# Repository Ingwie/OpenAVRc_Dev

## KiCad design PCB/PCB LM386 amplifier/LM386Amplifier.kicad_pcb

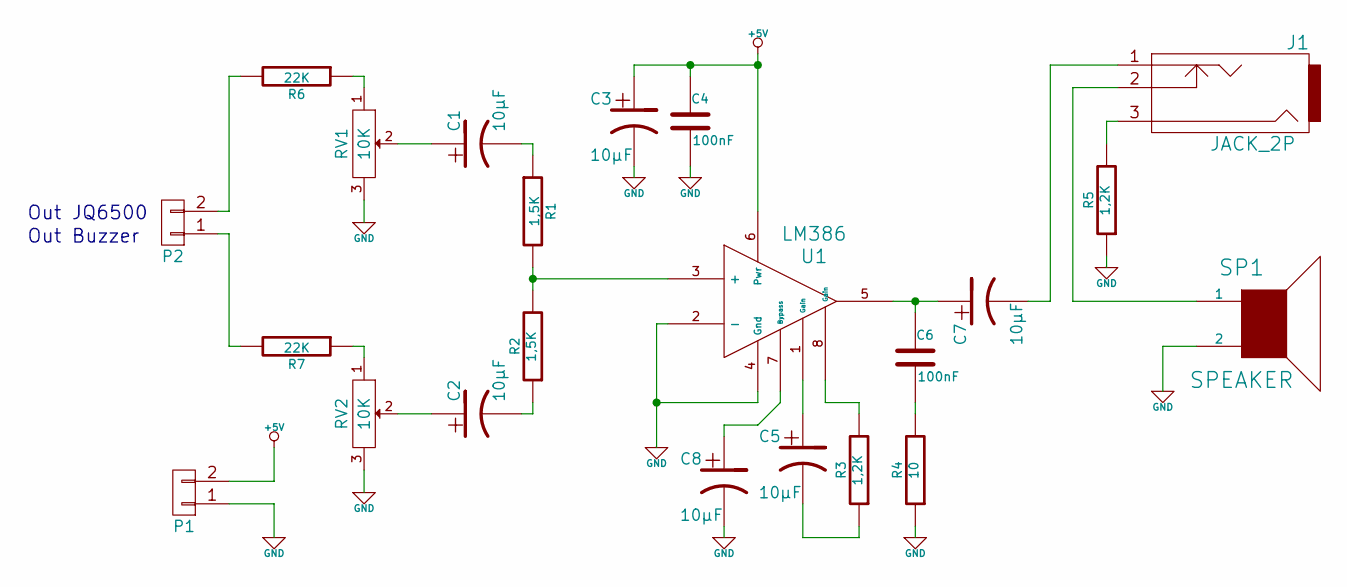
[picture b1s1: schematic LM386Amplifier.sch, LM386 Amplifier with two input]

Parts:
C1, C2, C3: 10µF; CP_Radial_D6.3mm_P2.50mm
C4, C6: 100nF; C_Rect_L7.0mm_W2.0mm_P5.00mm
C5, C7, C8: 10µF; CP_Radial_Tantal_D6.0mm_P2.50mm
J1: JACK_2P; Pin_Header_Straight_1x03_Pitch2.54mm
P1, P2: CONN_01X02; Pin_Header_Straight_1x02_Pitch2.54mm
R1, R2: 1,5K; R_Axial_DIN0204_L3.6mm_D1.6mm_P2.54mm_Vertical
R3, R5: 1,2K; R_Axial_DIN0204_L3.6mm_D1.6mm_P2.54mm_Vertical
R4: 10; R_Axial_DIN0204_L3.6mm_D1.6mm_P2.54mm_Vertical
R6, R7: 22K; R_Axial_DIN0204_L3.6mm_D1.6mm_P2.54mm_Vertical
RV1, RV2: 10K; Potentiometer_Trimmer_Bourns_3296W.kicad_mod
SP1: SPEAKER; Pin_Header_Straight_1x02_Pitch2.54mm
U1: LM386; DIP-8_W7.62mm_LongPads

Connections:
+5V: C3.1, C4.1, P1.2, U1.6 (Pwr)
GND: C3.2, C4.2, C8.2, P1.1, R4.1, R5.1, RV1.3, RV2.3, SP1.2, U1.2 (-), U1.4 (Gnd)
unnamed: C1.1, RV1.2
unnamed: C1.2, R1.1
unnamed: C2.1, RV2.2
unnamed: C2.2, R2.1
unnamed: C5.1, U1.1 (Gain)
unnamed: C5.2, R3.1
unnamed: C6.1, C7.1, U1.5
unnamed: C6.2, R4.2
unnamed: C7.2, J1.1
unnamed: C8.1, U1.7 (Bypass)
unnamed: J1.2, SP1.1
unnamed: J1.3, R5.2
unnamed: P2.1, R7.2
unnamed: P2.2, R6.2
unnamed: R1.2, R2.2, U1.3 (+)
unnamed: R3.2, U1.8 (Gain)
unnamed: R6.1, RV1.1
unnamed: R7.1, RV2.1

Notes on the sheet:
Out Buzzer
Out JQ6500

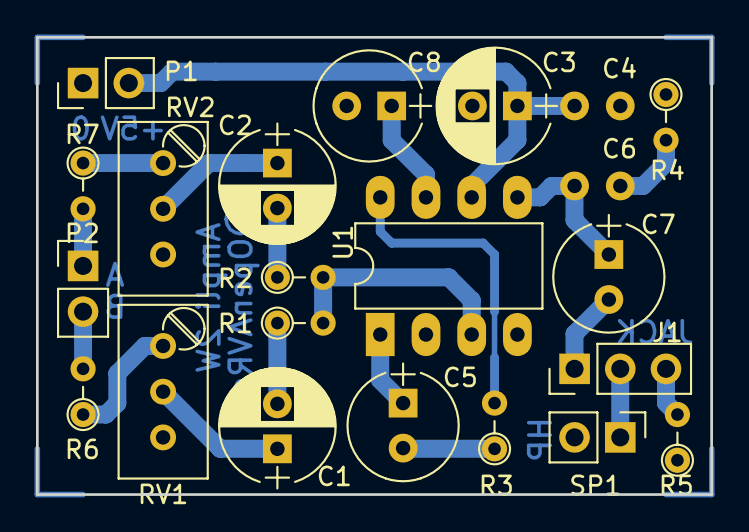
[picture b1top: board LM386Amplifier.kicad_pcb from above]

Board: 2 copper layers, 37.5 x 25.4 mm, 22 parts (0 on the bottom side), 20 nets.

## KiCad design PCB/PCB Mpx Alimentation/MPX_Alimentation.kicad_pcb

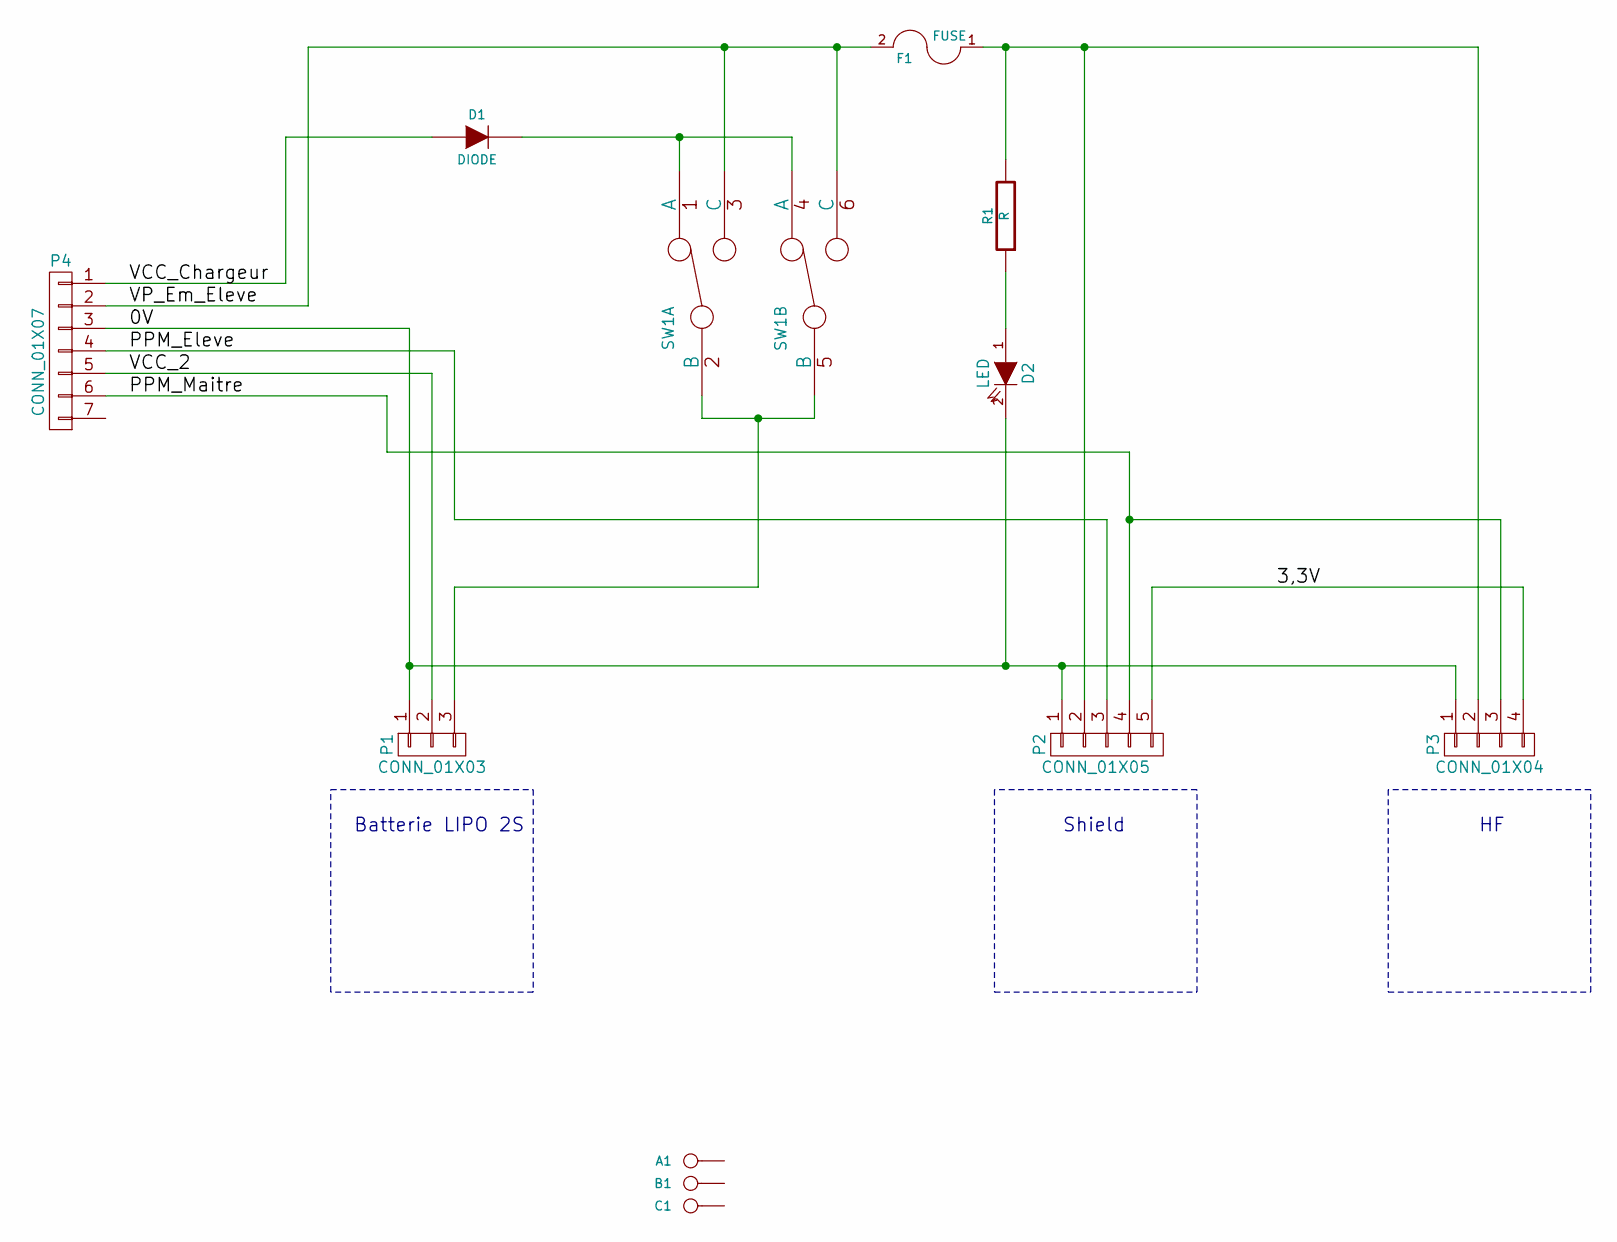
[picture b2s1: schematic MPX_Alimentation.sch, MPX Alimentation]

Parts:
A1: CONN_1; MountingHole_2.2mm_M2
B1: CONN_1; MountingHole_2.2mm_M2
C1: CONN_1; MountingHole_2.2mm_M2
D1: DIODE; D_DO-201_P15.24mm_Horizontal
D2: LED; LED_D3.0mm
F1: FUSE; Fuseholder5x20_horiz_open_universal_Type-III
P1: CONN_01X03; Pin_Header_Angled_1x03_Pitch2.54mm
P2: CONN_01X05; Pin_Header_Angled_1x05_Pitch2.54mm
P3: CONN_01X04; Pin_Header_Angled_1x04_Pitch2.54mm
P4: CONN_01X07; Embase_Din8_Mpx
R1: R; R_Axial_DIN0207_L6.3mm_D2.5mm_P10.16mm_Horizontal
SW1: DUAL_SWITCH_INV; SW_CuK_JS202011CQN_DPDT_Straight

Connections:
/0V: D2.2 (K), P1.1, P2.1, P3.1, P4.3
/3,3V: P2.5, P3.4
/PPM_Eleve: P2.3, P4.4
/PPM_Maitre: P2.4, P3.3, P4.6
/VCC_2: P1.2, P4.5
/VCC_Chargeur: D1.1 (A), P4.1
/VP_Em_Eleve: F1.2, P4.2, SW1.3 (C), SW1.6 (C)
unnamed: D1.2 (K), SW1.1 (A), SW1.4 (A)
unnamed: D2.1 (A), R1.1
unnamed: F1.1, P2.2, P3.2, R1.2
unnamed: P1.3, SW1.2 (B), SW1.5 (B)

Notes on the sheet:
Batterie LIPO 2S
Shield

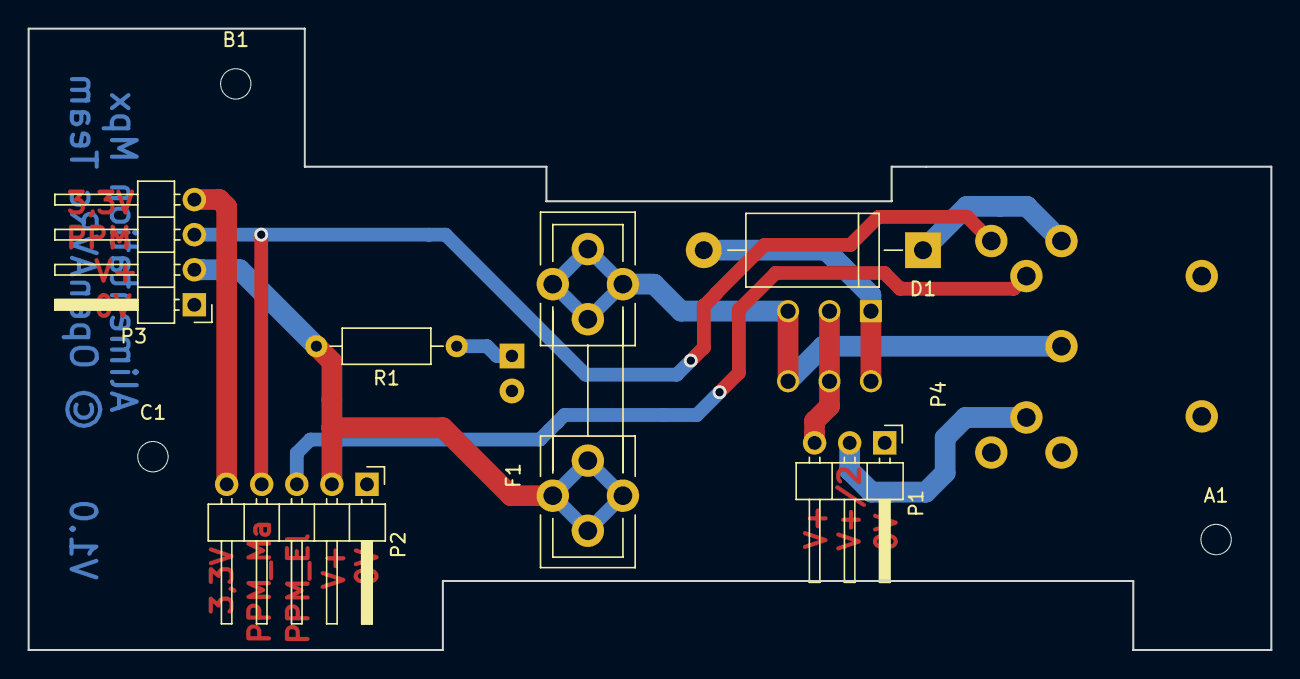
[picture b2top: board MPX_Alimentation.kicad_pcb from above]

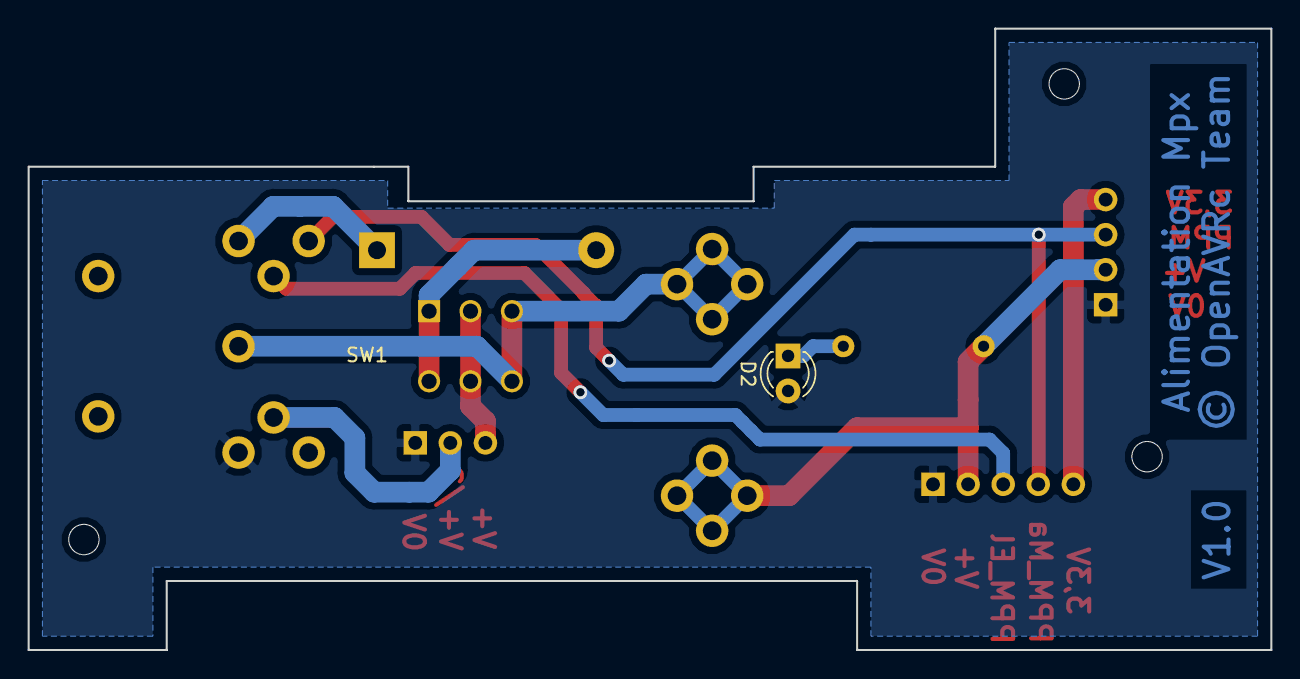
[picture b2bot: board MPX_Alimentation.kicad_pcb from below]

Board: 2 copper layers, 90.0 x 45.0 mm, 12 parts (2 on the bottom side), 11 nets.

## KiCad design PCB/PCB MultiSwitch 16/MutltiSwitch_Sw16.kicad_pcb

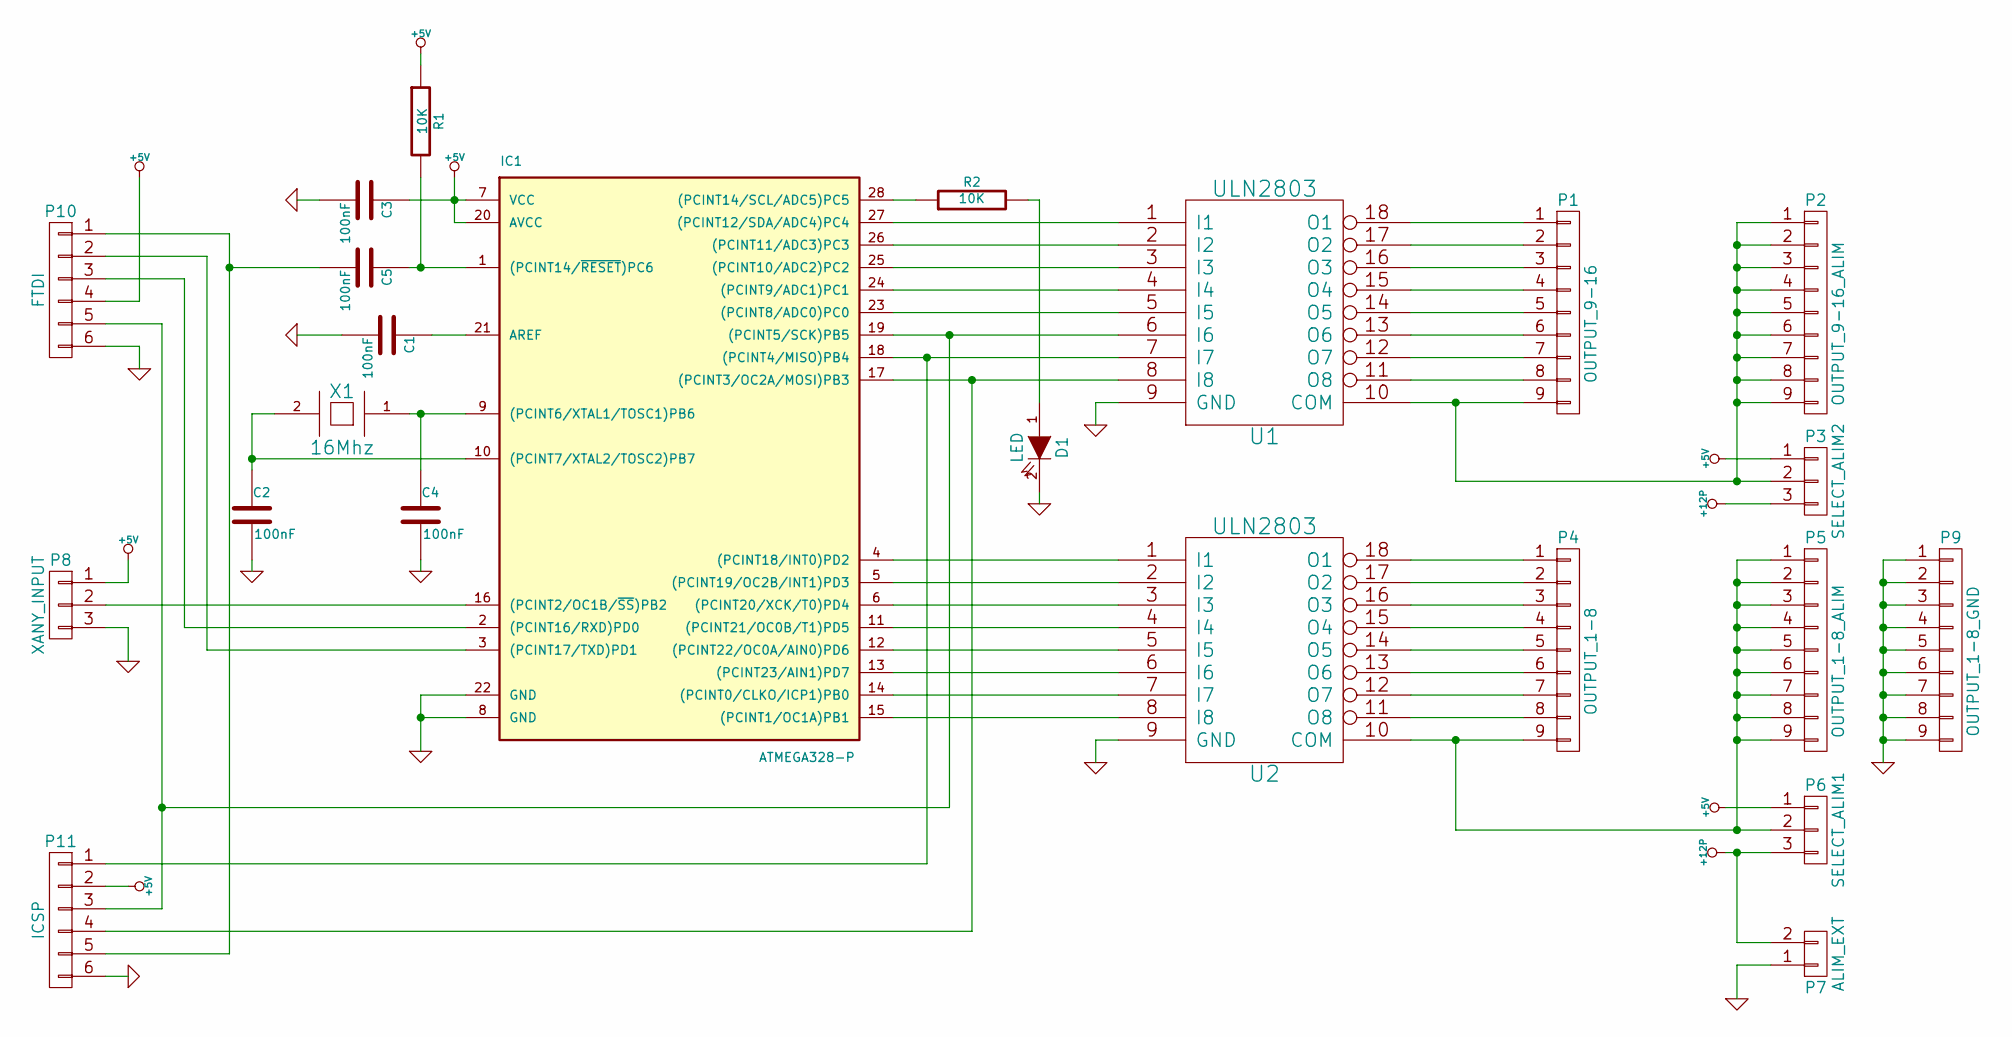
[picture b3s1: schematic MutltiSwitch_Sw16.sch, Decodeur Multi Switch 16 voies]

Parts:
C1, C2, C3, C4, C5: 100nF; C_1206
D1: LED; LED_1206
IC1: ATMEGA328-P; DIP-28_W7.62mm_LongPads
P1: OUTPUT_9-16; Pin_Header_Straight_1x09_Pitch2.54mm
P2: OUTPUT_9-16_ALIM; Pin_Header_Straight_1x09_Pitch2.54mm
P3: SELECT_ALIM2; Pin_Header_Straight_1x03_Pitch2.54mm
P4: OUTPUT_1-8; Pin_Header_Straight_1x09_Pitch2.54mm
P5: OUTPUT_1-8_ALIM; Pin_Header_Straight_1x09_Pitch2.54mm
P6: SELECT_ALIM1; Pin_Header_Straight_1x03_Pitch2.54mm
P7: ALIM_EXT; XT60_F
P8: XANY_INPUT; Pin_Header_Straight_1x03_Pitch2.54mm
P9: OUTPUT_1-8_GND; Pin_Header_Straight_1x09_Pitch2.54mm
P10: FTDI; Pin_Header_Straight_2x03_Pitch2.54mm
P11: ICSP; Pin_Header_Straight_2x03_Pitch2.54mm
R1, R2: 10K; R_1206
U1, U2: ULN2803; DIP-18_W7.62mm_LongPads
X1: 16Mhz; HC-39

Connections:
+5V: C3.1, IC1.7 (VCC), IC1.20 (AVCC), P3.1, P6.1, P8.1, P10.4, P11.2, R1.1
+12P: P3.3, P6.3, P7.2
GND: C1.2, C2.2, C3.2, C4.2, D1.2 (K), IC1.8 (GND), IC1.22 (GND), P7.1, P8.3, P9.1, P9.2, P9.3, P9.4, P9.5, P9.6, P9.7, P9.8, P9.9, P10.6, P11.6, U1.9 (GND), U2.9 (GND)
unnamed: C1.1, IC1.21 (AREF)
unnamed: C2.1, IC1.10 ((PCINT7/XTAL2/TOSC2)PB7), X1.2
unnamed: C4.1, IC1.9 ((PCINT6/XTAL1/TOSC1)PB6), X1.1
unnamed: C5.1, IC1.1 ((PCINT14/~RESET~)PC6), R1.2
unnamed: C5.2, P10.1, P11.5
unnamed: D1.1 (A), R2.2
unnamed: IC1.2 ((PCINT16/RXD)PD0), P10.3
unnamed: IC1.3 ((PCINT17/TXD)PD1), P10.2
unnamed: IC1.4 ((PCINT18/INT0)PD2), U2.1 (I1)
unnamed: IC1.5 ((PCINT19/OC2B/INT1)PD3), U2.2 (I2)
unnamed: IC1.6 ((PCINT20/XCK/T0)PD4), U2.3 (I3)
unnamed: IC1.11 ((PCINT21/OC0B/T1)PD5), U2.4 (I4)
unnamed: IC1.12 ((PCINT22/OC0A/AIN0)PD6), U2.5 (I5)
unnamed: IC1.13 ((PCINT23/AIN1)PD7), U2.6 (I6)
unnamed: IC1.14 ((PCINT0/CLKO/ICP1)PB0), U2.7 (I7)
unnamed: IC1.15 ((PCINT1/OC1A)PB1), U2.8 (I8)
unnamed: IC1.16 ((PCINT2/OC1B/~SS~)PB2), P8.2
unnamed: IC1.17 ((PCINT3/OC2A/MOSI)PB3), P11.4, U1.8 (I8)
unnamed: IC1.18 ((PCINT4/MISO)PB4), P11.1, U1.7 (I7)
unnamed: IC1.19 ((PCINT5/SCK)PB5), P10.5, P11.3, U1.6 (I6)
unnamed: IC1.23 ((PCINT8/ADC0)PC0), U1.5 (I5)
unnamed: IC1.24 ((PCINT9/ADC1)PC1), U1.4 (I4)
unnamed: IC1.25 ((PCINT10/ADC2)PC2), U1.3 (I3)
unnamed: IC1.26 ((PCINT11/ADC3)PC3), U1.2 (I2)
unnamed: IC1.27 ((PCINT12/SDA/ADC4)PC4), U1.1 (I1)
unnamed: IC1.28 ((PCINT14/SCL/ADC5)PC5), R2.1
unnamed: P1.1, U1.18 (O1)
unnamed: P1.2, U1.17 (O2)
unnamed: P1.3, U1.16 (O3)
unnamed: P1.4, U1.15 (O4)
unnamed: P1.5, U1.14 (O5)
unnamed: P1.6, U1.13 (O6)
unnamed: P1.7, U1.12 (O7)
unnamed: P1.8, U1.11 (O8)
unnamed: P1.9, P2.1, P2.2, P2.3, P2.4, P2.5, P2.6, P2.7, P2.8, P2.9, P3.2, U1.10 (COM)
unnamed: P4.1, U2.18 (O1)
unnamed: P4.2, U2.17 (O2)
unnamed: P4.3, U2.16 (O3)
unnamed: P4.4, U2.15 (O4)
unnamed: P4.5, U2.14 (O5)
unnamed: P4.6, U2.13 (O6)
unnamed: P4.7, U2.12 (O7)
unnamed: P4.8, U2.11 (O8)
unnamed: P4.9, P5.1, P5.2, P5.3, P5.4, P5.5, P5.6, P5.7, P5.8, P5.9, P6.2, U2.10 (COM)

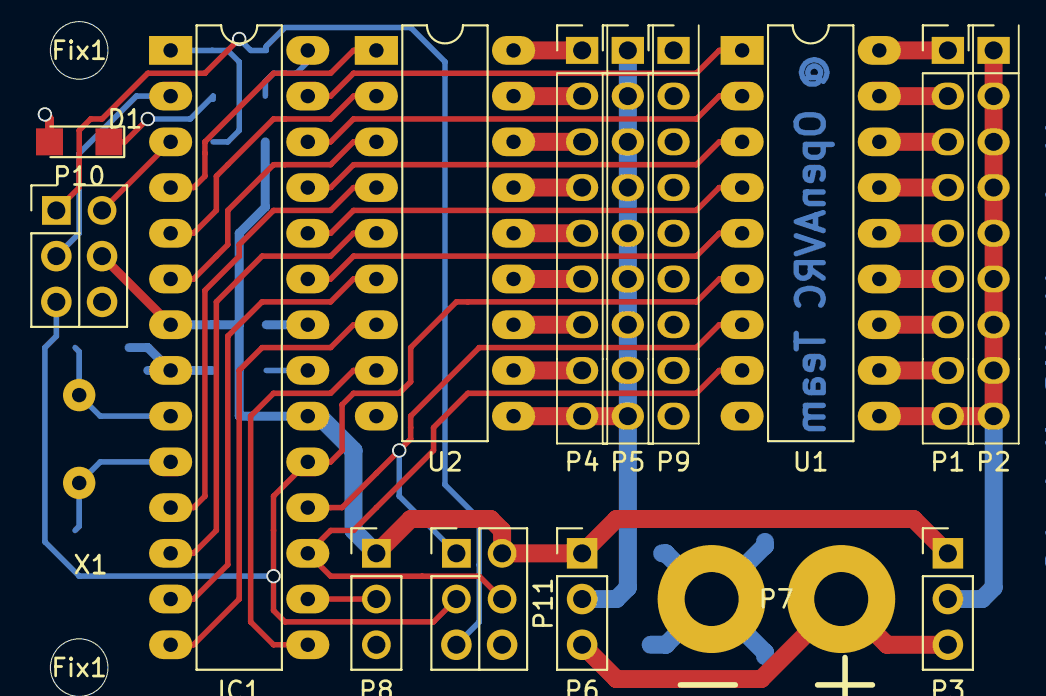
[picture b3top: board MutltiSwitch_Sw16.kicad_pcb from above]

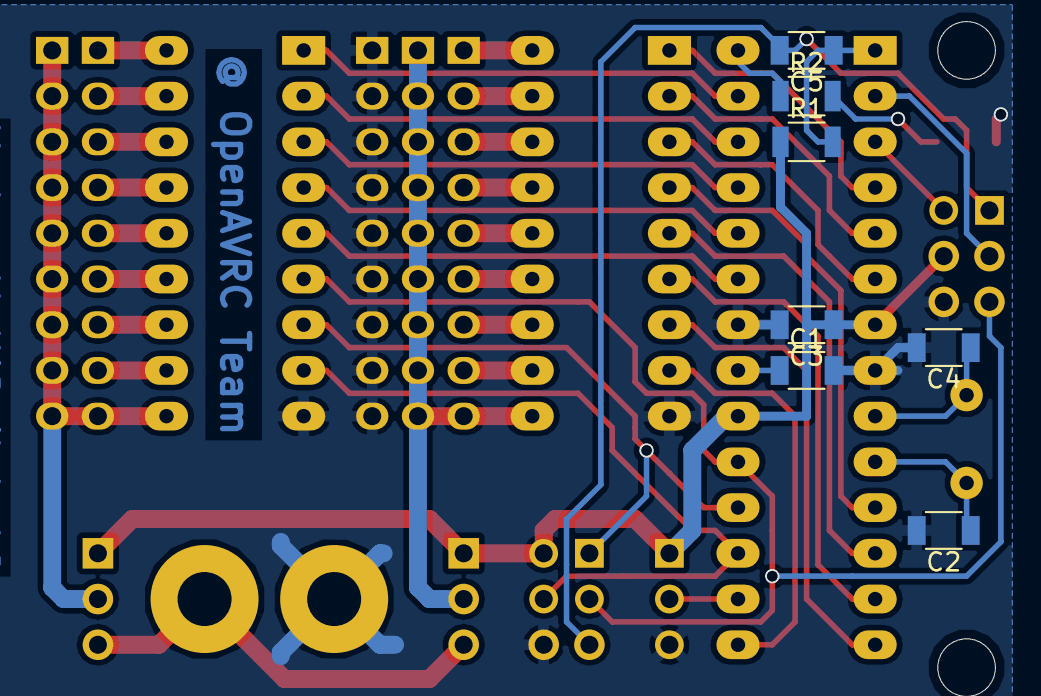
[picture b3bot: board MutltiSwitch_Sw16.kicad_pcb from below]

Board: 2 copper layers, 27 parts (7 on the bottom side), 47 nets.

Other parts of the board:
Fix1, Fix1#2, Fix1#3, Fix1#4: MountingHole_3.2mm_M3

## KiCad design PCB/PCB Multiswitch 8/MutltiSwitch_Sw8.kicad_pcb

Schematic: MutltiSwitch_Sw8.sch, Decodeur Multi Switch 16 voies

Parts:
C1, C2, C3: 100nF; C_1206
D1: LED; LED_1206
IC1: ATTINY84-P; DIP-14_W7.62mm_LongPads
IC2: ULN2803; DIP-18_W7.62mm_LongPads
P1: OUTPUT_1-8; Pin_Header_Straight_1x09_Pitch2.54mm
P8: XANY_INPUT; Pin_Header_Straight_1x03_Pitch2.54mm
R2: 470; R_1206
X1: 16Mhz; HC-39

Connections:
+5V: C1.1, IC1.1 (VCC), P8.2
GND: C1.2, C2.2, C3.2, D1.2 (K), IC1.14 (GND), IC2.9 (GND), P8.3
unnamed: C2.1, IC1.3 ((PCINT9/XTAL2)PB1), X1.2
unnamed: C3.1, IC1.2 ((PCINT8/CLKI/XTAL1)PB0), X1.1
unnamed: D1.1 (A), R2.2
unnamed: IC1.4 ((PCINT11/dW/~RESET~)PB3), R2.1
unnamed: IC1.5 ((PCINT10/CKOUT/OC0A/INT0)PB2), P8.1
unnamed: IC1.6 ((PCINT7/ICP/OC0B/ADC7)PA7), IC2.8 (I8)
unnamed: IC1.7 ((PCINT6/SDA/DI/MOSI/OC1A/ADC6)PA6), IC2.7 (I7)
unnamed: IC1.8 ((PCINT5/DO/MISO/OC1B/ADC5)PA5), IC2.6 (I6)
unnamed: IC1.9 ((PCINT4/USCK/SCL/T1/ADC4)PA4), IC2.5 (I5)
unnamed: IC1.10 ((PCINT3/T0/ADC3)PA3), IC2.4 (I4)
unnamed: IC1.11 ((PCINT2/AIN1/ADC2)PA2), IC2.3 (I3)
unnamed: IC1.12 ((PCINT1/AIN0/ADC1)PA1), IC2.2 (I2)
unnamed: IC1.13 ((PCINT0/AREF/ADC0)PA0), IC2.1 (I1)
unnamed: IC2.10 (COM), P1.9
unnamed: IC2.11 (O8), P1.8
unnamed: IC2.12 (O7), P1.7
unnamed: IC2.13 (O6), P1.6
unnamed: IC2.14 (O5), P1.5
unnamed: IC2.15 (O4), P1.4
unnamed: IC2.16 (O3), P1.3
unnamed: IC2.17 (O2), P1.2
unnamed: IC2.18 (O1), P1.1

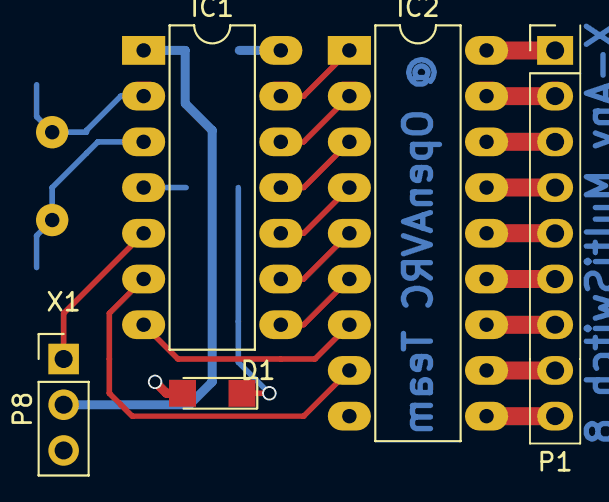
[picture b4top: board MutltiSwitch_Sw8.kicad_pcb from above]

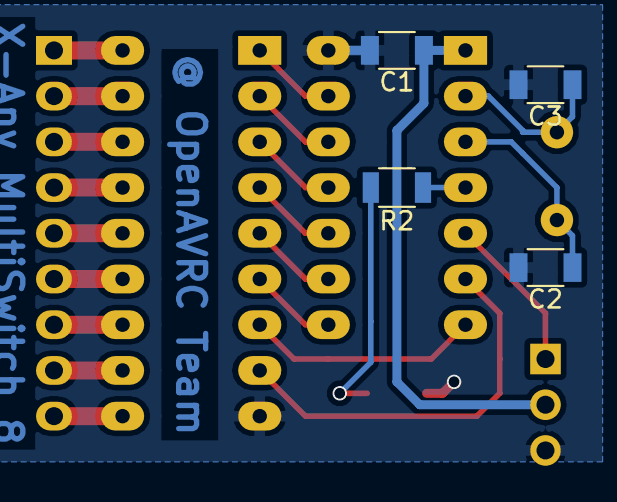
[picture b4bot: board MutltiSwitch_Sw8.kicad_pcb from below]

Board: 2 copper layers, 10 parts (4 on the bottom side), 24 nets.

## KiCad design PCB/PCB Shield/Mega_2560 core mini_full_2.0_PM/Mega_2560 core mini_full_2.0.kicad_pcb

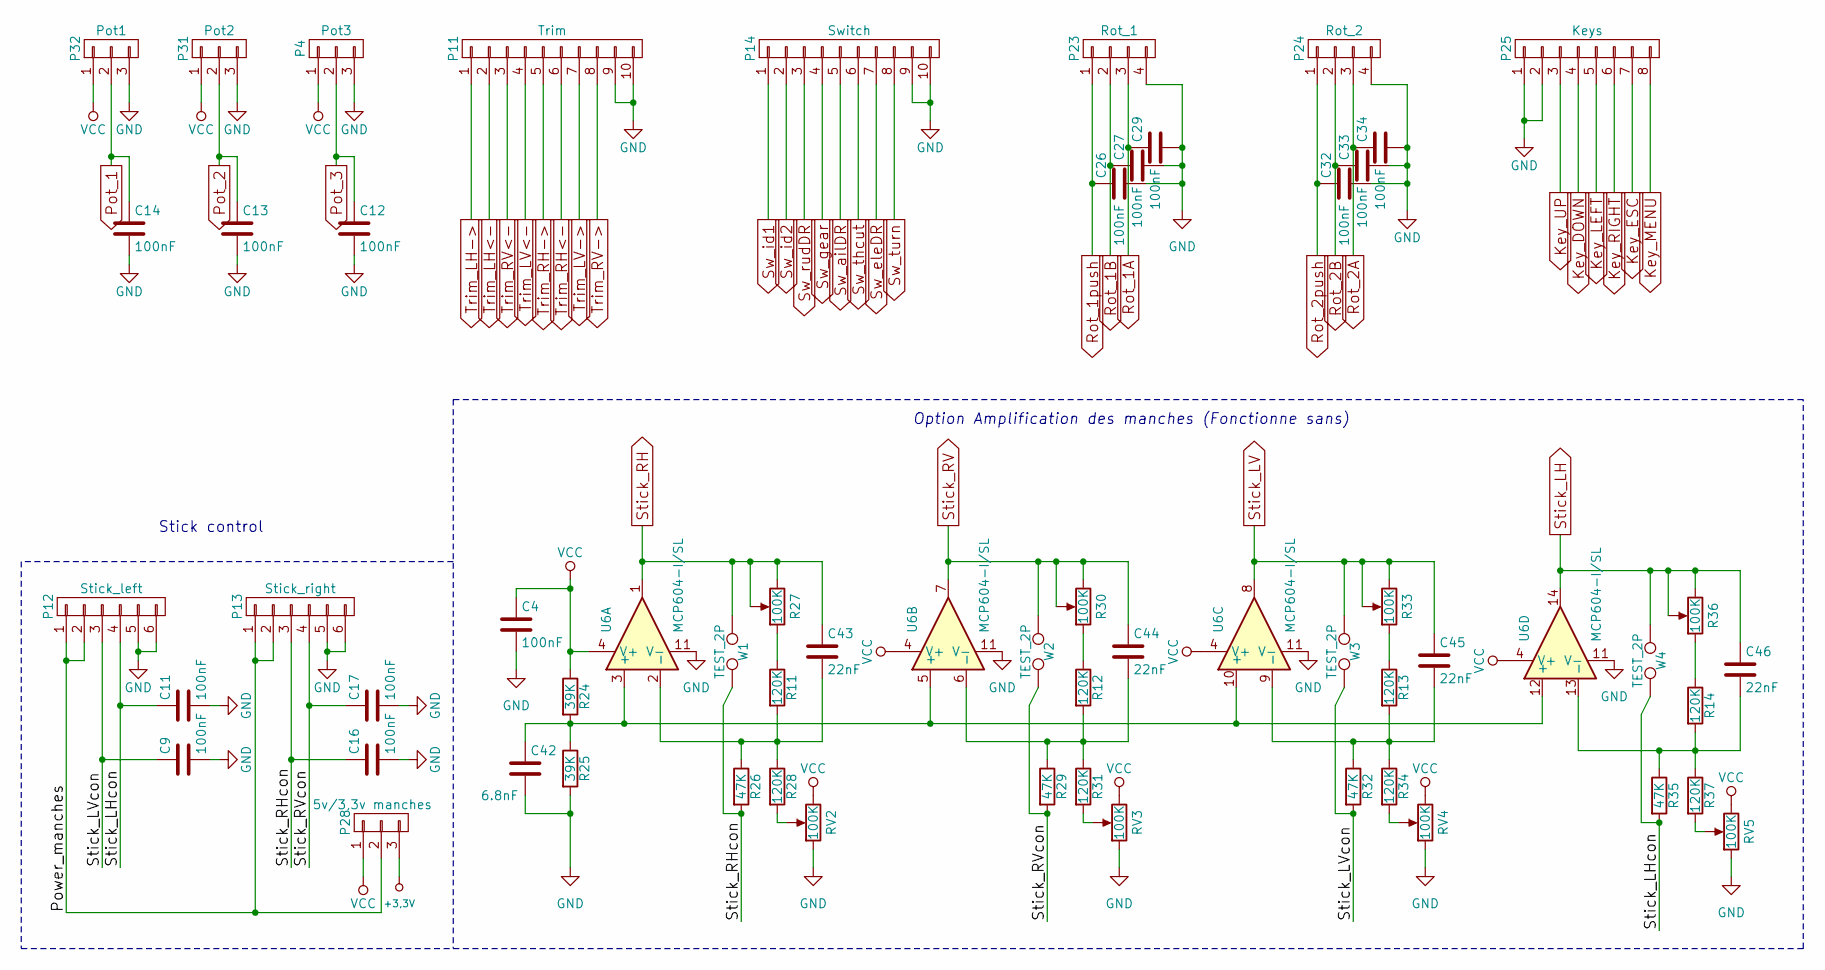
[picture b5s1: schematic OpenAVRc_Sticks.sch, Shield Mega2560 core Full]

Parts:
C4, C9, C11, C12, C13, C14, C16, C17, C26, C27, C29, C32, C33, C34: 100nF; C_1206
C42: 6.8nF; C_1206
C43, C44, C45, C46: 22nF; C_1206
P4: Pot3; Pin_Header_Straight_1x03_Pitch2.54mm
P11: Trim; Pin_Header_Straight_2x05_Pitch2.54mm
P12: Stick_left; Pin_Header_Straight_2x03_Pitch2.54mm
P13: Stick_right; Pin_Header_Straight_1x06_Pitch2.54mm
P14: Switch; Pin_Header_Straight_2x05_Pitch2.54mm
P23: Rot_1; Pin_Header_Straight_1x04_Pitch2.54mm
P24: Rot_2; Pin_Header_Straight_1x04_Pitch2.54mm
P25: Keys; Pin_Header_Straight_2x04_Pitch2.54mm
P28: 5v/3,3v manches; Pin_Header_Straight_1x03_Pitch2.54mm
P31: Pot2; Pin_Header_Straight_1x03_Pitch2.54mm
P32: Pot1; Pin_Header_Straight_1x03_Pitch2.54mm
R11, R12, R13, R14, R28, R31, R34, R37: 120K; R_1206
R24, R25: 39K; R_1206
R26, R29, R32, R35: 47K; R_1206
R27, R30, R33, R36: 100K; Potentiometer_Trimmer_Bourns_3296W
RV2, RV3, RV4, RV5: 100K; Potentiometer_Bourns_3296W_3-8Zoll_Inline_ScrewUp
U6: MCP604-I/SL; SOP14
W1, W2, W3, W4: TEST_2P; TESTPT

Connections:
+3.3V: P28.3; also elsewhere on the board
/OpenAVRc_Sticks/Power_manches: P12.1, P12.2, P13.1, P13.2, P28.2
/OpenAVRc_Sticks/Stick_LHcon: C11.1, P12.4, R35.2, W4.2
/OpenAVRc_Sticks/Stick_LVcon: C9.1, P12.3, R32.2, W3.2
/OpenAVRc_Sticks/Stick_RHcon: C16.1, P13.3, R26.2, W1.2
/OpenAVRc_Sticks/Stick_RVcon: C17.1, P13.4, R29.2, W2.2
GND: C4.2, C9.2, C11.2, C12.2, C13.2, C14.2, C16.2, C17.2, C26.2, C27.2, C29.2, C32.2, C33.2, C34.2, C42.2, P4.3, P11.9, P11.10, P12.5, P12.6, P13.5, P13.6, P14.9, P14.10, P23.4, P24.4, P25.1, P25.2, P31.3, P32.3, R25.2, RV2.1, RV3.1, RV4.1, RV5.1, U6.11 (V-); also elsewhere on the board
Key_DOWN: P25.4; also elsewhere on the board
Key_ESC: P25.7; also elsewhere on the board
Key_LEFT: P25.5; also elsewhere on the board
Key_MENU: P25.8; also elsewhere on the board
Key_RIGHT: P25.6; also elsewhere on the board
Key_UP: P25.3; also elsewhere on the board
unnamed: C42.1, R24.2, R25.1, U6.3 (+), U6.5 (+), U6.10 (+), U6.12 (+)
unnamed: C43.2, R11.2, R26.1, R28.1, U6.2 (-)
unnamed: C44.2, R12.2, R29.1, R31.1, U6.6 (-)
unnamed: C45.2, R13.2, R32.1, R34.1, U6.9 (-)
unnamed: C46.2, R14.2, R35.1, R37.1, U6.13 (-)
unnamed: R11.1, R27.1
unnamed: R12.1, R30.1
unnamed: R13.1, R33.1
unnamed: R14.1, R36.1
unnamed: R28.2, RV2.2
unnamed: R31.2, RV3.2
unnamed: R34.2, RV4.2
unnamed: R37.2, RV5.2
Pot_1: C14.1, P32.2; also elsewhere on the board
Pot_2: C13.1, P31.2; also elsewhere on the board
Pot_3: C12.1, P4.2; also elsewhere on the board
Rot_1A: C29.1, P23.3; also elsewhere on the board
Rot_1B: C27.1, P23.2; also elsewhere on the board
Rot_1push: C26.1, P23.1; also elsewhere on the board
Rot_2A: C34.1, P24.3; also elsewhere on the board
Rot_2B: C33.1, P24.2; also elsewhere on the board
Rot_2push: C32.1, P24.1; also elsewhere on the board
Stick_LH: C46.1, R36.2, R36.3, U6.14, W4.1; also elsewhere on the board
Stick_LV: C45.1, R33.2, R33.3, U6.8, W3.1; also elsewhere on the board
Stick_RH: C43.1, R27.2, R27.3, U6.1, W1.1; also elsewhere on the board
Stick_RV: C44.1, R30.2, R30.3, U6.7, W2.1; also elsewhere on the board
Sw_ailDR: P14.5; also elsewhere on the board
Sw_eleDR: P14.7; also elsewhere on the board
Sw_gear: P14.4; also elsewhere on the board
Sw_id1: P14.1; also elsewhere on the board
Sw_id2: P14.2; also elsewhere on the board
Sw_rudDR: P14.3; also elsewhere on the board
Sw_thcut: P14.6; also elsewhere on the board
Sw_turn: P14.8; also elsewhere on the board
Trim_LH->: P11.1; also elsewhere on the board
Trim_LH<-: P11.2; also elsewhere on the board
Trim_LV->: P11.7; also elsewhere on the board
Trim_LV<-: P11.4; also elsewhere on the board
Trim_RH->: P11.5; also elsewhere on the board
Trim_RH<-: P11.6; also elsewhere on the board
Trim_RV->: P11.8; also elsewhere on the board
Trim_RV<-: P11.3; also elsewhere on the board
VCC: C4.1, P4.1, P28.1, P31.1, P32.1, R24.1, RV2.3, RV3.3, RV4.3, RV5.3, U6.4 (V+); also elsewhere on the board

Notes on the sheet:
Stick control
Option Amplification des manches (Fonctionne sans)

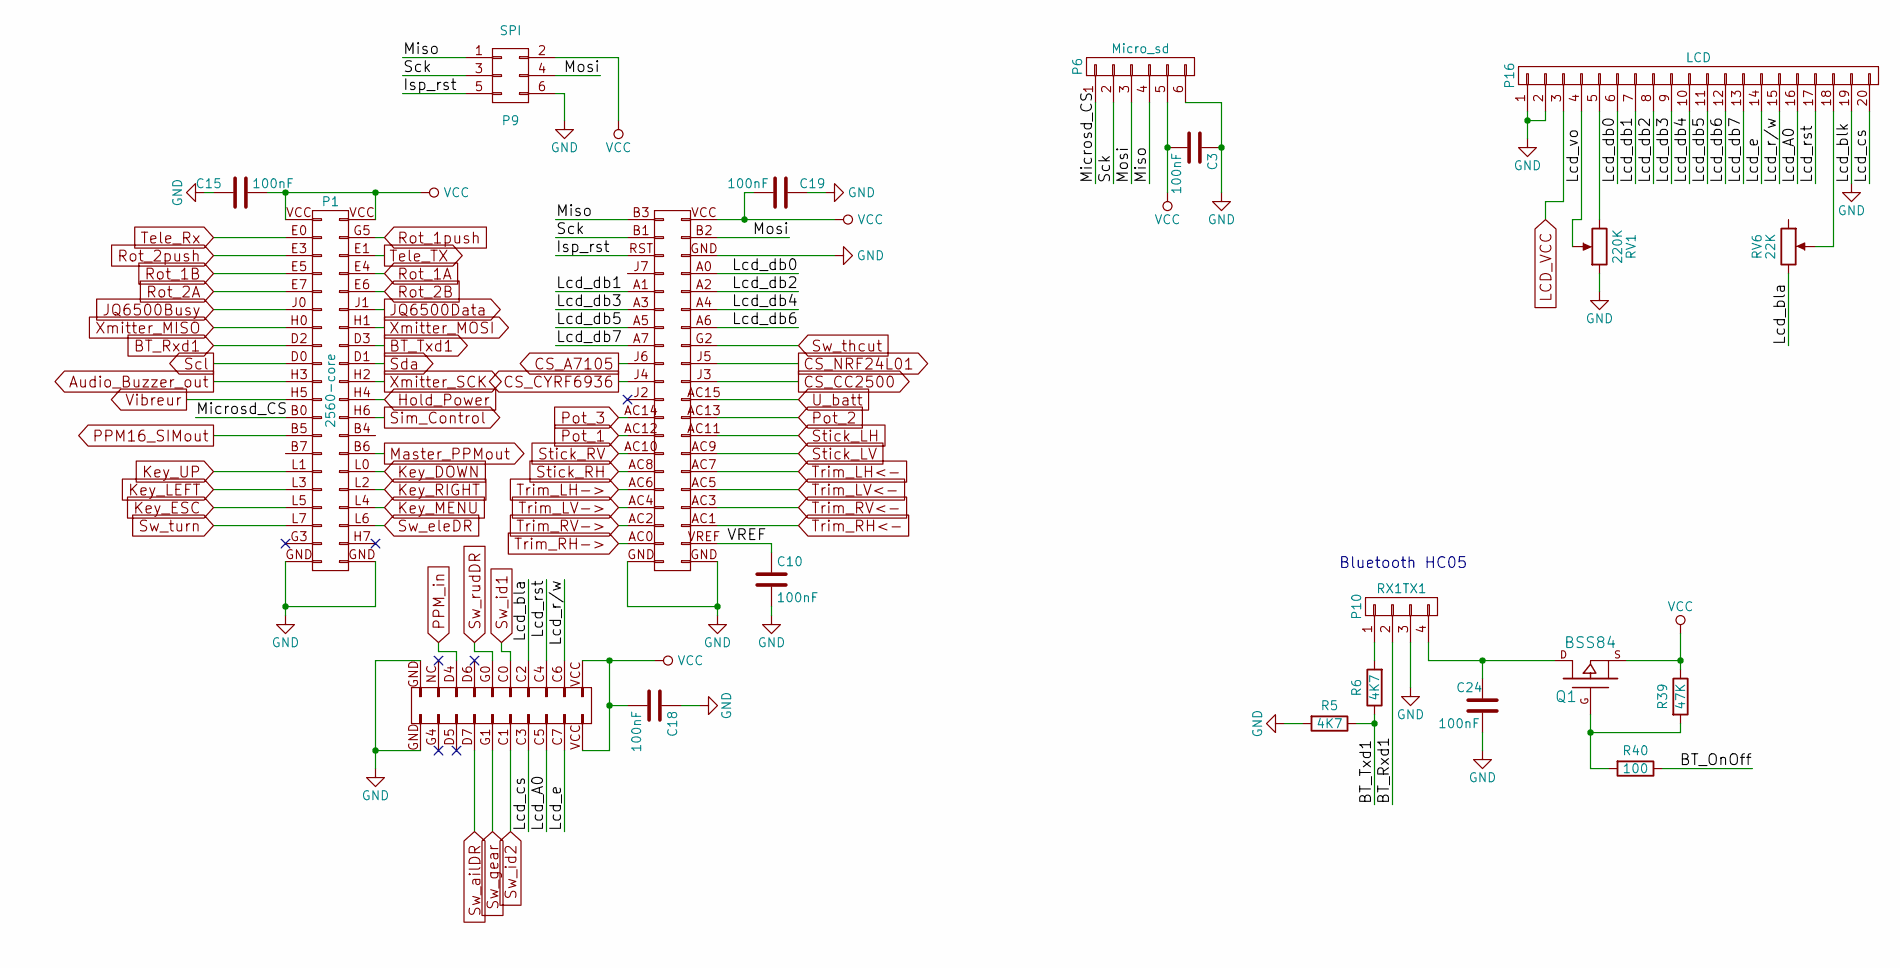
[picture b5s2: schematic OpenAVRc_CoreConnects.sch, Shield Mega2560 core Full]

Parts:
C3, C10, C15, C18, C19, C24: 100nF; C_1206
P1: 2560-core; Connectors-2560-core
P6: Micro_sd; Pin_Header_Straight_1x06_Pitch2.54mm
P9: SPI; Pin_Header_Straight_2x03_Pitch2.54mm
P10: RX1TX1; Pin_Header_Straight_1x04_Pitch2.54mm
P16: LCD; Pin_Header_Straight_2x10_Pitch2.54mm
Q1: BSS84
R5, R6: 4K7; R_1206
R39: 47K; R_1206
R40: 100; R_1206
RV1: 220K; Potentiometer_Trimmer_Bourns_3296W
RV6: 22K; Potentiometer_Trimmer_Bourns_3296W

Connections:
/OpenAVRc_CoreConnects/Isp_rst: P1.RST (P75), P9.5
/OpenAVRc_CoreConnects/Lcd_A0: P1.C5 (P85), P16.16
/OpenAVRc_CoreConnects/Lcd_bla: P1.C2 (P88), RV6.3
/OpenAVRc_CoreConnects/Lcd_cs: P1.C3 (P87), P16.20
/OpenAVRc_CoreConnects/Lcd_db0: P1.A0 (P74), P16.6
/OpenAVRc_CoreConnects/Lcd_db1: P1.A1 (P71), P16.7
/OpenAVRc_CoreConnects/Lcd_db2: P1.A2 (P72), P16.8
/OpenAVRc_CoreConnects/Lcd_db3: P1.A3 (P69), P16.9
/OpenAVRc_CoreConnects/Lcd_db4: P1.A4 (P70), P16.10
/OpenAVRc_CoreConnects/Lcd_db5: P1.A5 (P67), P16.11
/OpenAVRc_CoreConnects/Lcd_db6: P1.A6 (P68), P16.12
/OpenAVRc_CoreConnects/Lcd_db7: P1.A7 (P65), P16.13
/OpenAVRc_CoreConnects/Lcd_e: P1.C7 (P83), P16.14
/OpenAVRc_CoreConnects/Lcd_r/w: P1.C6 (P84), P16.15
/OpenAVRc_CoreConnects/Lcd_rst: P1.C4 (P86), P16.17
/OpenAVRc_CoreConnects/Lcd_vo: P16.4, RV1.2
/OpenAVRc_CoreConnects/Microsd_CS: P1.B0 (P24), P6.1
/OpenAVRc_CoreConnects/Miso: P1.B3 (P79), P6.4, P9.1
/OpenAVRc_CoreConnects/Mosi: P1.B2 (P78), P6.3, P9.4
/OpenAVRc_CoreConnects/Sck: P1.B1 (P77), P6.2, P9.3
/OpenAVRc_CoreConnects/VREF: C10.1, P1.VREF (P44)
Audio_Buzzer_out: P1.H3 (P20); also elsewhere on the board
BT_Rxd1: P1.D2 (P16), P10.2
BT_Txd1: P1.D3 (P15), R5.1, R6.1
CS_A7105: P1.J6 (P63); also elsewhere on the board
CS_CC2500: P1.J3 (P62); also elsewhere on the board
CS_CYRF6936: P1.J4 (P61); also elsewhere on the board
CS_NRF24L01: P1.J5 (P64); also elsewhere on the board
GND: C3.1, C10.2, C15.1, C18.1, C19.1, C24.2, P1.GND (P100), P6.6, P9.6, P10.3, P16.1, P16.2, P16.19, R5.2, RV1.1; also elsewhere on the board
Hold_Power: P1.H4 (P21); also elsewhere on the board
JQ6500Busy: P1.J0 (P12); also elsewhere on the board
JQ6500Data: P1.J1 (P11); also elsewhere on the board
Key_DOWN: P1.L0 (P29); also elsewhere on the board
Key_ESC: P1.L5 (P34); also elsewhere on the board
Key_LEFT: P1.L3 (P32); also elsewhere on the board
Key_MENU: P1.L4 (P33); also elsewhere on the board
Key_RIGHT: P1.L2 (P31); also elsewhere on the board
Key_UP: P1.L1 (P30); also elsewhere on the board
LCD_VCC: P16.3; also elsewhere on the board
Master_PPMout: P1.B6 (P27); also elsewhere on the board
unnamed: C24.1, P10.4, Q1.D
unnamed: P10.1, R6.2
unnamed: P16.5, RV1.3
unnamed: P16.18, RV6.2
unnamed: Q1.G, R39.2, R40.2
PPM16_SIMout: P1.B5 (P26); also elsewhere on the board
PPM_in: P1.D4 (P96); also elsewhere on the board
Pot_1: P1.AC12 (P55); also elsewhere on the board
Pot_2: P1.AC13 (P58); also elsewhere on the board
Pot_3: P1.AC14 (P57); also elsewhere on the board
Rot_1A: P1.E4 (P7); also elsewhere on the board
Rot_1B: P1.E5 (P8); also elsewhere on the board
Rot_1push: P1.G5 (P3); also elsewhere on the board
Rot_2A: P1.E7 (P10); also elsewhere on the board
Rot_2B: P1.E6 (P9); also elsewhere on the board
Rot_2push: P1.E3 (P6); also elsewhere on the board
Scl: P1.D0 (P18); also elsewhere on the board
Sda: P1.D1 (P17); also elsewhere on the board
Sim_Control: P1.H6 (P23); also elsewhere on the board
Stick_LH: P1.AC11 (P56); also elsewhere on the board
Stick_LV: P1.AC9 (P54); also elsewhere on the board
Stick_RH: P1.AC8 (P51); also elsewhere on the board
Stick_RV: P1.AC10 (P53); also elsewhere on the board
Sw_ailDR: P1.D7 (P93); also elsewhere on the board
Sw_eleDR: P1.L6 (P35); also elsewhere on the board
Sw_gear: P1.G1 (P91); also elsewhere on the board
Sw_id1: P1.C0 (P90); also elsewhere on the board
Sw_id2: P1.C1 (P89); also elsewhere on the board
Sw_rudDR: P1.G0 (P92); also elsewhere on the board
Sw_thcut: P1.G2 (P66); also elsewhere on the board
Sw_turn: P1.L7 (P36); also elsewhere on the board
Tele_RX: P1.E0 (P4); also elsewhere on the board
Tele_TX: P1.E1 (P5); also elsewhere on the board
Trim_LH->: P1.AC6 (P49); also elsewhere on the board
Trim_LH<-: P1.AC7 (P52); also elsewhere on the board
Trim_LV->: P1.AC4 (P47); also elsewhere on the board
Trim_LV<-: P1.AC5 (P50); also elsewhere on the board
Trim_RH->: P1.AC0 (P43); also elsewhere on the board
Trim_RH<-: P1.AC1 (P46); also elsewhere on the board
Trim_RV->: P1.AC2 (P45); also elsewhere on the board
Trim_RV<-: P1.AC3 (P48); also elsewhere on the board
U_batt: P1.AC15 (P60); also elsewhere on the board
VCC: C3.2, C15.2, C18.2, C19.2, P1.VCC (P1), P6.5, P9.2, Q1.S, R39.1; also elsewhere on the board
Vibreur: P1.H5 (P22); also elsewhere on the board
Xmitter_MISO: P1.H0 (P14); also elsewhere on the board
Xmitter_MOSI: P1.H1 (P13); also elsewhere on the board
Xmitter_SCK: P1.H2 (P19); also elsewhere on the board

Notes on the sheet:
Bluetooth HC05

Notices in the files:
PCB/PCB LM386 amplifier/LM386Amplifier.kicad_pcb:
©OpenAVRc
PCB/PCB LM386 amplifier/LM386Amplifier.sch:
©OpenAVRc Team
PCB/PCB Shield/Mega_2560 core mini_full_2.0_PM/OpenAVRc_Audio_Haptic.sch:
© Team OpenAVRc
